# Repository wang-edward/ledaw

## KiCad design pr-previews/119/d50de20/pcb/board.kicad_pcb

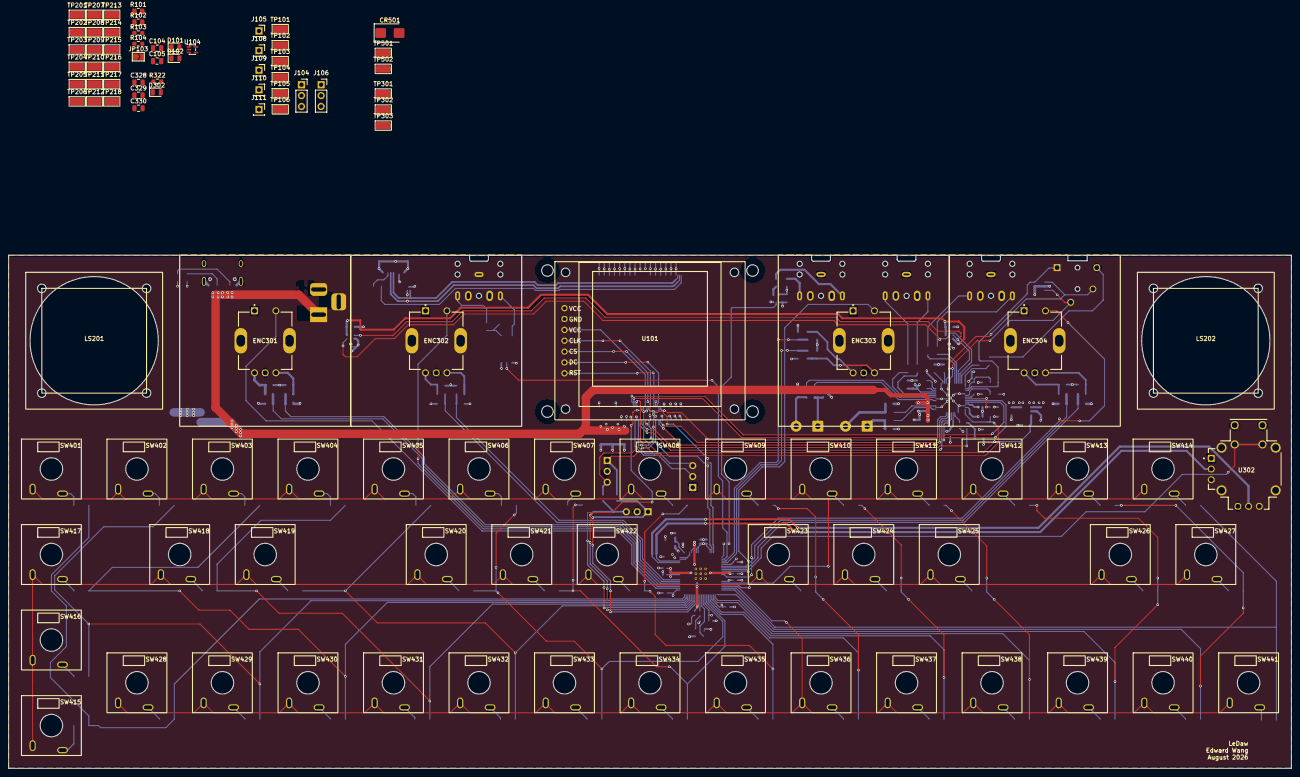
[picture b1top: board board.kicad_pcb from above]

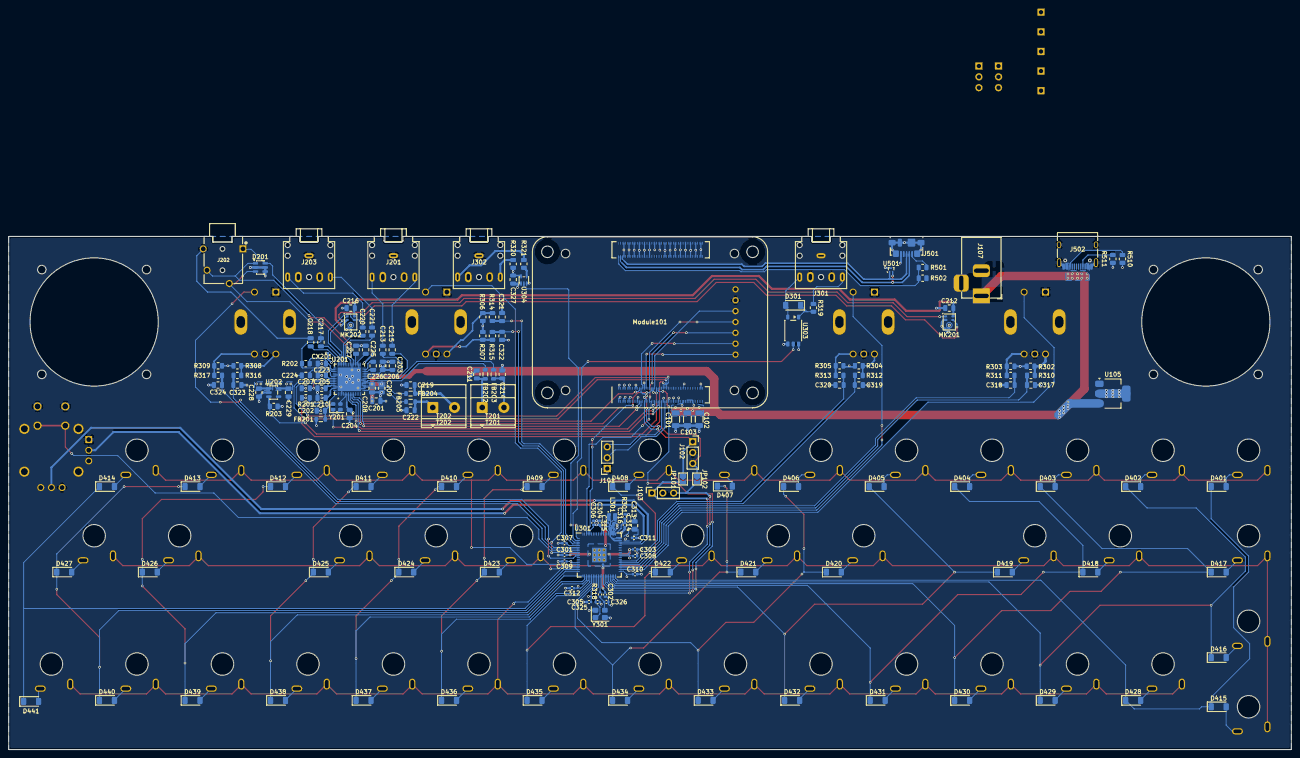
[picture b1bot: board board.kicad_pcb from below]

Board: 4 copper layers, 300.0 x 120.0 mm, 265 parts (164 on the bottom side), 172 nets.

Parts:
C101, C102, C103: 22uF X5R 16V; C_1206_3216Metric
C104: 10 uF, 10 V, X7R ceramic; C_0805_2012Metric
C105: 10-22 µF, 10 V tantalum, ESR 0.033-2.2 Ω over ope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; C_0805_2012Metric
C201, C203, C213, C215, C313: 10uF; C_0805_2012Metric
C202, C204, C210, C212, C216, C327, C328, C329, C330: 100nF; C_0805_2012Metric
C205, C206, C207, C208, C209, C217, C218, C220, C221, C223, C225, C226, C227, C228, C229: 1uF; C_0805_2012Metric
C211, C214, C219, C222: 470pF; C_0805_2012Metric
C224: 2.2uF; C_0805_2012Metric
C301, C303, C304, C305, C306, C307, C308, C309, C310, C311, C312: 100nF; C_0402_1005Metric
C302, C314: 4.7uF; C_0402_1005Metric
C315, C316: 4.7uF; C_0402_1005Metric_small_pads
C317, C318, C319, C320, C321, C322, C323, C324: 10nF; C_0805_2012Metric
C325, C326: 15pF; C_0402_1005Metric
CR501: SMBJ5.0A-TR; D_SMB
CX201: 1uF; C_0805_2012Metric
D101: LED Green; LED_0805_2012Metric
D102: LED Red; LED_0805_2012Metric
D201: ESDA6V1BC6; SOT-23-6
D301, D401, D402, D403, D404, D405, D406, D407, D408, D409, D410, D411, D412, D413, D414, D415, D416, D417, D418, D419, D420, D421, D422, D423, D424, D425, D426, D427, D428, D429, D430, D431, D432, D433, D434, D435, D436, D437, D438, D439, D440, D441: LL4148; D_MiniMELF
D302: LED Blue; LED_0805_2012Metric
ENC301, ENC302, ENC303, ENC304: RotaryEncoder_Switch; XDCR_PEC11R-4015F-S0024
FB201, FB202, FB203, FB204, FB205: 600Ohm@100MHz; L_0805_2012Metric
J101: CM4_UART; PinSocket_1x03_P2.54mm_Vertical
J102: CM4_DEBUG; PinSocket_1x03_P2.54mm_Vertical
J103: MCU_DEBUG; PinSocket_1x03_P2.54mm_Vertical
J104: MCU_UART; PinSocket_1x03_P2.54mm_Vertical
J105: MCU_RUN; PinSocket_1x01_P2.54mm_Vertical
J106: CM4_STATUS; PinSocket_1x03_P2.54mm_Vertical
J107: Barrel_5V; DC-005-5A-2.0
J108: TP_3V3; PinSocket_1x01_P2.54mm_Vertical
J109: TP_1V8; PinSocket_1x01_P2.54mm_Vertical
J110: TP_5V; PinSocket_1x01_P2.54mm_Vertical
J111: TP_GND; PinSocket_1x01_P2.54mm_Vertical
J201: LineOut; Jack_3.5mm_CUI_SJ1-3525N_Horizontal
J202: Headphone; CUI_SJ-43514
J203: LineIn; Jack_3.5mm_CUI_SJ1-3525N_Horizontal
J301: MidiIn; Jack_3.5mm_CUI_SJ1-3525N_Horizontal
J302: MidiOut; Jack_3.5mm_CUI_SJ1-3525N_Horizontal
J501: USB_B_Micro; USB_Micro-B_Molex_47346-0001
J502: USB_C_Receptacle_PowerOnly_24P; USB_C_Receptacle_HRO_TYPE-C-31-M-12
JP101, JP103: Jumper_SWCLK_Open; SolderJumper-2_P1.3mm_Open_TrianglePad1.0x1.5mm
JP102: Jumper_SWD_Open; SolderJumper-2_P1.3mm_Open_TrianglePad1.0x1.5mm
L301: 3.3uH; L_pol_2016
LS201: SpeakerL; bf-32-s-8ohm
LS202: SpeakerR; bf-32-s-8ohm
MK201: MicL; Knowles_LGA-5_3.5x2.65mm
MK202: MicR; Knowles_LGA-5_3.5x2.65mm
Module101: ComputeModule4-CM4; Raspberry-Pi-4-Compute-Module
R101, R102: 1k; R_0805_2012Metric
R103, R104: 4.7k; R_0603_1608Metric_Pad0.98x0.95mm_HandSolder
R201, R203, R302, R303, R304, R305, R306, R307, R308, R309, R310, R311, R312, R313, R314, R315, R316, R317: 10k; R_0805_2012Metric
R202: 2.2k; R_0805_2012Metric
R301: 33; R_0402_1005Metric
R318: 1k; R_0402_1005Metric
R319: 220; R_0805_2012Metric
R320: 33; R_0805_2012Metric
R321: 10; R_0805_2012Metric
R322: 1k; R_0603_1608Metric_Pad0.98x0.95mm_HandSolder
R501, R502: 2.2K 1%; R_0805_2012Metric
R510, R511: 5.1k; R_0805_2012Metric
SW401, SW402, SW403, SW404, SW405, SW406, SW407, SW408, SW409, SW410, SW411, SW412, SW413, SW414, SW415, SW416, SW417, SW418, SW419, SW420, SW421, SW422, SW423, SW424, SW425, SW426, SW427, SW428, SW429, SW430, SW431, SW432, SW433, SW434, SW435, SW436, SW437, SW438, SW439, SW440, SW441: SW_Push; ks-33-2.0
T201: TerminalL; TerminalBlock_Phoenix_MKDS-1,5-2-5.08_1x02_P5.08mm_Horizont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
T202: TerminalR; TerminalBlock_Phoenix_MKDS-1,5-2-5.08_1x02_P5.08mm_Horizont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
TP101: LDO_IN; TestPoint_Keystone_5015_Micro_Mini
TP102: LDO_OUT; TestPoint_Keystone_5015_Micro_Mini
TP103: CM4_5V; TestPoint_Keystone_5015_Micro_Mini
TP104: MCU_3V3_OUTPUT; TestPoint_Keystone_5015_Micro_Mini
TP105: MCU_1V8_OUTPUT; TestPoint_Keystone_5015_Micro_Mini
TP106: nLED_ACTIVITY; TestPoint_Keystone_5015_Micro_Mini
TP201: CODEC_MCLK; TestPoint_Keystone_5015_Micro_Mini
TP202: SPKLP; TestPoint_Keystone_5015_Micro_Mini
TP203: JACKSENSE; TestPoint_Keystone_5015_Micro_Mini
TP204: RECP; TestPoint_Keystone_5015_Micro_Mini
TP205: SPKLN; TestPoint_Keystone_5015_Micro_Mini
TP206: RECN; TestPoint_Keystone_5015_Micro_Mini
TP207: MICBIAS; TestPoint_Keystone_5015_Micro_Mini
TP208, TP213: INA1; TestPoint_Keystone_5015_Micro_Mini
TP209: HPR; TestPoint_Keystone_5015_Micro_Mini
TP210: SPKRP; TestPoint_Keystone_5015_Micro_Mini
TP211, TP215: INA2; TestPoint_Keystone_5015_Micro_Mini
TP212: HPL; TestPoint_Keystone_5015_Micro_Mini
TP214: HPSNS; TestPoint_Keystone_5015_Micro_Mini
TP216: SPKRN; TestPoint_Keystone_5015_Micro_Mini
TP217: AUDIO_LDO_IN; TestPoint_Keystone_5015_Micro_Mini
TP218: AUDIO_LDO_OUT; TestPoint_Keystone_5015_Micro_Mini
TP301: MCU_3V3; TestPoint_Keystone_5015_Micro_Mini
TP302: MCU_1V1; TestPoint_Keystone_5015_Micro_Mini
TP303: MCU_VREG_AVDD; TestPoint_Keystone_5015_Micro_Mini
TP501: VBUS; TestPoint_Keystone_5015_Micro_Mini
TP502: USB_OTG_ID; TestPoint_Keystone_5015_Micro_Mini
U101: Oled; waveshare-1.5inch-oled
U104: 74LVC1G07SE-7; SOT-353_SC-70-5
U105: NCP1117-3.3_SOT223; SOT-223-3_TabPin2
U201: MAX98089ETN_T
U202: TPS7A2018PDBVR; SOT-23-5
U301: RP2354B_80QFN; RP2350-QFN-80-1EP_10x10_P0.4mm_EP3.4x3.4mm_ThermalVias
U302: THB001P
U303: TLP2310; SO-5-6_4.55x3.7mm_P1.27mm
U304: 74AHC1G125DCKR; SOT-353_SC-70-5
U501: TPD2EUSB30; Texas_DRT-3
Y201: 12.288MHz; Oscillator_SMD_SeikoEpson_SG210-4Pin_2.5x2.0mm
Y301: ABM8-272-T3; Crystal_SMD_3225-4Pin_3.2x2.5mm

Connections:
+1V1: C301.1, C302.1, C303.1, C316.1, L301.1, TP302.1 (1_1), U301.10 (DVDD), U301.32 (DVDD), U301.51 (DVDD), U301.65 (VREG_FB)
+1V8: C203.2, C205.2, C206.2, C207.2, C212.2, C216.2, C229.1, J109.1 (Pin_1_1), MK201.5 (VDD), MK202.2 (SEL), MK202.5 (VDD), TP218.1 (1_1), U201.25 (PVDD), U201.50 (AVDD), U201.53 (DVDD), U202.5 (OUT)
+3V3: C105.1, C204.2, C210.2, C228.1, C304.1, C305.1, C306.1, C307.1, C308.1, C309.1, C310.1, C311.1, C312.1, C313.1, C315.1, C327.1, C328.1, D101.2 (A), D102.2 (A), D302.2 (A), FB201.2, J108.1 (Pin_1_1), JP103.1 (A), R103.1, R104.1, R201.2, R301.1, R302.1, R303.1, R304.1, R305.1, R306.1, R307.1, R308.1, R309.1, R320.2, TP102.1 (1_1), TP217.1 (1_1), TP301.1 (1_1), U101.1 (VCC), U104.5 (VCC), U105.2 (VO), U201.6 (DVDDS1), U201.55 (DVDDS2), U202.1 (IN), U301.5 (IOVDD), U301.15 (IOVDD), U301.24 (IOVDD), U301.29 (IOVDD), U301.41 (IOVDD), U301.50 (IOVDD), U301.59 (ADC_AVDD), U301.60 (IOVDD), U301.64 (VREG_VIN), U301.68 (USB_OTP_VDD), U301.69 (QSPI_IOVDD), U301.76 (IOVDD), U302.VR1_3, U302.VR2_3, U303.6 (VDD), U304.5 (VCC)
+5V: C101.1, C102.1, C103.1, C104.1, C201.2, C208.2, C209.2, CR501.1, J107.1, J110.1 (Pin_1_1), J502.A4 (VBUS), J502.A9 (VBUS), J502.B4 (VBUS), J502.B9 (VBUS), Module101.77 (+5v_(Input)), Module101.79 (+5v_(Input)), Module101.81 (+5v_(Input)), Module101.83 (+5v_(Input)), Module101.85 (+5v_(Input)), Module101.87 (+5v_(Input)), TP101.1 (1_1), TP103.1 (1_1), TP501.1 (1_1), U105.3 (VI), U201.18 (SPKRVDD), U201.19 (SPKLVDD)
/CODEC_1V8EN: Module101.46 (GPIO22), R203.1, U202.3 (EN)
/CODEC_CLKEN: Module101.47 (GPIO23), Y201.1 (OE)
/CODEC_~IRQ: Module101.54 (GPIO4), R201.1, U201.56 (~IRQ)
/DC: Module101.30 (GPIO6), U101.6 (DC)
/Global_EN: J106.1, Module101.99 (Global_EN)
/I2C1_SCL: Module101.56 (GPIO3), R104.2, U201.51 (SCL)
/I2C1_SDA: Module101.58 (GPIO2), R103.2, U201.52 (SDA)
/MCU_SWCLK: J103.1, JP101.2 (B), U301.33 (SWCLK)
/MCU_SWD: J103.3, JP102.2 (B), U301.34 (SWD)
/PCM_CLK: Module101.49 (GPIO18), U201.8 (BCLKS1)
/PCM_DIN: Module101.27 (GPIO20), U201.7 (SDOUTS1)
/PCM_DOUT: Module101.25 (GPIO21), U201.9 (SDINS1)
/PCM_FS: Module101.26 (GPIO19), U201.10 (LRCLKS1)
/RST: Module101.34 (GPIO5), U101.7 (RST)
/RUN: J105.1 (Pin_1_1), JP103.2 (B), Module101.48 (GPIO27), U301.35 (RUN)
/RUN_PG: J106.2, Module101.92 (RUN_PG)
/SPI0_CE1: Module101.37 (GPIO7), U101.5 (CS)
/SPI0_MOSI: Module101.44 (GPIO10), U101.3 (DIN)
/SPI0_SCLK: Module101.38 (GPIO11), U101.4 (CLK)
/SWCLK: J102.1, JP101.1 (A), Module101.31 (GPIO12)
/SWD: J102.3, JP102.1 (A), Module101.28 (GPIO13)
/UART0_RX: J101.3, Module101.51 (GPIO15)
/UART0_TX: J101.2, Module101.55 (GPIO14)
/UART4_RX: J104.2, Module101.40 (GPIO9), U301.77 (GPIO0)
/UART4_TX: J104.3, Module101.39 (GPIO8), U301.78 (GPIO1)
/USB2_N: J501.2 (D-), Module101.103 (USB2_N), U501.2 (D-)
/USB2_OTG_ID: Module101.101 (USB_OTG_ID), R501.2, R502.1, TP502.1 (1_1)
/USB2_P: J501.3 (D+), Module101.105 (USB2_P), U501.1 (D+)
/audio/C1N: C226.1, U201.27 (C1N)
/audio/C1P: C226.2, U201.26 (C1P)
/audio/DIGMICCLK: MK201.4 (CLOCK), MK202.4 (CLOCK), U201.41 (MIC1N/DIGMICCLK)
/audio/DIGMICDATA: MK201.1 (DATA), MK202.1 (DATA), U201.40 (MIC1P/DIGMICDATA)
/audio/JACKSENSE: C217.1, D201.6 (TVS4), J202.S, R202.2, TP203.1 (1_1), U201.45 (JACKSNS)
/mcu/ENC1_A: C317.1, R310.2, U301.44 (GPIO35)
/mcu/ENC1_B: C318.1, R311.2, U301.45 (GPIO36)
/mcu/ENC1_SW: ENC301.S2, U301.42 (GPIO33)
/mcu/ENC2_A: C319.1, R312.2, U301.46 (GPIO37)
/mcu/ENC2_B: C320.1, R313.2, U301.47 (GPIO38)
/mcu/ENC2_SW: ENC302.S2, U301.43 (GPIO34)
/mcu/ENC3_A: C321.1, R314.2, U301.3 (GPIO6)
/mcu/ENC3_B: C322.1, R315.2, U301.4 (GPIO7)
/mcu/ENC3_SW: ENC303.S2, U301.9 (GPIO11)
/mcu/ENC4_A: C323.1, R316.2, U301.6 (GPIO8)
/mcu/ENC4_B: C324.1, R317.2, U301.7 (GPIO9)
/mcu/ENC4_SW: ENC304.S2, U301.11 (GPIO12)
/mcu/HEARTBEAT: R322.2, U301.48 (GPIO39)
/mcu/JOYSTICK_SW: U301.8 (GPIO10), U302.A, U302.B
/mcu/JOYSTICK_X: C329.1, U301.58 (GPIO47_ADC7), U302.VR1_2
/mcu/JOYSTICK_Y: C330.1, U301.57 (GPIO46_ADC6), U302.VR2_2
/mcu/MIDI_RX: U301.2 (GPIO5), U303.5 (VO)
/mcu/MIDI_TX: U301.1 (GPIO4), U304.2
/mcu/VREG_AVDD: C314.1, R301.2, TP303.1 (1_1), U301.61 (VREG_AVDD)
/mcu/VREG_LX: L301.2, U301.63 (VREG_LX)
/mcu/XIN: C325.1, U301.30 (XIN), Y301.1
/mcu/XOUT: R318.1, U301.31 (XOUT)
/mcu/matrix_C0: D401.1 (K), D415.1 (K), D428.1 (K), U301.40 (GPIO32)
/mcu/matrix_C1: D402.1 (K), D416.1 (K), D429.1 (K), U301.39 (GPIO31)
/mcu/matrix_C2: D403.1 (K), D417.1 (K), D430.1 (K), U301.38 (GPIO30)
/mcu/matrix_C3: D404.1 (K), D418.1 (K), D431.1 (K), U301.37 (GPIO29)
/mcu/matrix_C4: D405.1 (K), D419.1 (K), D432.1 (K), U301.36 (GPIO28)
/mcu/matrix_C5: D406.1 (K), D420.1 (K), D433.1 (K), U301.28 (GPIO27)
/mcu/matrix_C6: D407.1 (K), D421.1 (K), D434.1 (K), U301.27 (GPIO26)
/mcu/matrix_C7: D408.1 (K), D422.1 (K), D435.1 (K), U301.26 (GPIO25)
/mcu/matrix_C8: D409.1 (K), D423.1 (K), D436.1 (K), U301.25 (GPIO24)
/mcu/matrix_C9: D410.1 (K), D424.1 (K), D437.1 (K), U301.23 (GPIO23)
/mcu/matrix_C10: D411.1 (K), D425.1 (K), D438.1 (K), U301.22 (GPIO22)
/mcu/matrix_C11: D412.1 (K), D426.1 (K), D439.1 (K), U301.21 (GPIO21)
/mcu/matrix_C12: D413.1 (K), D427.1 (K), D440.1 (K), U301.20 (GPIO20)
/mcu/matrix_C13: D414.1 (K), D441.1 (K), U301.19 (GPIO19)
/mcu/matrix_R0: SW401.1, SW402.1, SW403.1, SW404.1, SW405.1, SW406.1, SW407.1, SW408.1, SW409.1, SW410.1, SW411.1, SW412.1, SW413.1, SW414.1, U301.16 (GPIO16)
/mcu/matrix_R1: SW415.1, SW416.1, SW417.1, SW418.1, SW419.1, SW420.1, SW421.1, SW422.1, SW423.1, SW424.1, SW425.1, SW426.1, SW427.1, U301.17 (GPIO17)
/mcu/matrix_R2: SW428.1, SW429.1, SW430.1, SW431.1, SW432.1, SW433.1, SW434.1, SW435.1, SW436.1, SW437.1, SW438.1, SW439.1, SW440.1, SW441.1, U301.18 (GPIO18)
/nLED_Activity: Module101.21 (PI_nLED_Activity), R101.2, TP106.1 (1_1)
/nPWR_LED: Module101.95 (nPI_LED_PWR), U104.2
/nRPIBOOT: J106.3, Module101.93 (nRPIBOOT)
GND: C101.2, C102.2, C103.2, C104.2, C105.2, C201.1, C202.1, C203.1, C204.1, C205.1, C206.1, C207.1, C208.1, C209.1, C210.1, C211.2, C212.1, C214.2, C216.1, C218.1, C219.2, C222.2, C223.2, C224.2, C225.2, C227.2, C228.2, C229.2, C301.2, C302.2, C303.2, C304.2, C305.2, C306.2, C307.2, C308.2, C309.2, C310.2, C311.2, C312.2, C313.2, C314.2, C315.2, C316.2, C317.2, C318.2, C319.2, C320.2, C321.2, C322.2, C323.2, C324.2, C325.2, C326.2, C327.2, C328.2, C329.2, C330.2, CR501.2, CX201.1, D201.2 (COM), D201.4 (TVS3), D201.5 (COM), ENC301.C, ENC301.S1, ENC302.C, ENC302.S1, ENC303.C, ENC303.S1, ENC304.C, ENC304.S1, J101.1, J102.2, J103.2, J104.1, J107.2, J111.1 (Pin_1_1), J201.S, J202.R2, J203.S, J302.S, J501.5 (GND), J501.SH (Shield), J502.A1 (GND), J502.A12 (GND), J502.B1 (GND), J502.B12 (GND), J502.SH (SHIELD), MK201.2 (SEL), MK201.3 (GND), MK202.3 (GND), Module101.1 (GND), Module101.2 (GND), Module101.7 (GND), Module101.8 (GND), Module101.13 (GND), Module101.14 (GND), Module101.22 (GND), Module101.23 (GND), Module101.32 (GND), Module101.33 (GND), Module101.42 (GND), Module101.43 (GND), Module101.52 (GND), Module101.53 (GND), Module101.59 (GND), Module101.60 (GND), Module101.65 (GND), Module101.66 (GND), Module101.71 (GND), Module101.74 (GND), Module101.98 (GND), Module101.107 (GND), Module101.108 (GND), Module101.113 (GND), Module101.114 (GND), Module101.119 (GND), Module101.120 (GND), Module101.125 (GND), Module101.126 (GND), Module101.131 (GND), Module101.132 (GND), Module101.137 (GND), Module101.138 (GND), Module101.144 (GND), Module101.150 (GND), Module101.155 (GND), Module101.156 (GND), Module101.161 (GND), Module101.162 (GND), Module101.167 (GND), Module101.168 (GND), Module101.173 (GND), Module101.174 (GND), Module101.179 (GND), Module101.180 (GND), Module101.185 (GND), Module101.186 (GND), Module101.191 (GND), Module101.192 (GND), Module101.197 (GND), Module101.198 (GND), R203.2, R502.2, R510.2, R511.2, TP214.1 (1_1), U101.2 (GND), U104.3 (GND), U105.1 (GND), U201.3 (DGND), U201.16 (SPKRGND), U201.21 (SPKLGND), U201.30 (HPGND), U201.34 (HPSNS), U201.47 (AGND), U201.54 (SDINS2), U201.57 (EP), U202.2 (GND), U301.62 (VREG_PGND), U301.81 (GND), U302.C, U302.D, U302.VR1_1, U302.VR2_1, U303.4 (GND), U304.1, U304.3 (GND), U501.3 (GND), Y201.2 (GND), Y301.2, Y301.4
unnamed: C213.2, J201.T, TP204.1 (1_1)
unnamed: C215.2, J201.R, TP206.1 (1_1)
unnamed: C220.1, J203.T
unnamed: C221.1, J203.R
unnamed: C326.1, R318.2, Y301.3
unnamed: D101.1 (K), R101.1
unnamed: D102.1 (K), R102.1
unnamed: D201.1 (TVS1), J202.T, TP212.1 (1_1), U201.33 (HPL)
unnamed: D201.3 (TVS2), J202.R1, TP209.1 (1_1), U201.35 (HPR)
unnamed: D301.2 (A), J301.T, U303.3 (K)
unnamed: D301.1 (K), R319.2, U303.1 (A)
unnamed: D302.1 (K), R322.1
unnamed: D401.2 (A), SW401.2
unnamed: D402.2 (A), SW402.2
unnamed: D403.2 (A), SW403.2
unnamed: D404.2 (A), SW404.2
unnamed: D405.2 (A), SW405.2
unnamed: D406.2 (A), SW406.2
unnamed: D407.2 (A), SW407.2
unnamed: D408.2 (A), SW408.2
unnamed: D409.2 (A), SW409.2
unnamed: D410.2 (A), SW410.2
unnamed: D411.2 (A), SW411.2
unnamed: D412.2 (A), SW412.2
unnamed: D413.2 (A), SW413.2
unnamed: D414.2 (A), SW414.2
unnamed: D415.2 (A), SW415.2
unnamed: D416.2 (A), SW416.2
unnamed: D417.2 (A), SW417.2
unnamed: D418.2 (A), SW418.2
unnamed: D419.2 (A), SW419.2
unnamed: D420.2 (A), SW420.2
unnamed: D421.2 (A), SW421.2
unnamed: D422.2 (A), SW422.2
unnamed: D423.2 (A), SW423.2
unnamed: D424.2 (A), SW424.2
unnamed: D425.2 (A), SW425.2
unnamed: D426.2 (A), SW426.2
unnamed: D427.2 (A), SW427.2
unnamed: D428.2 (A), SW428.2
unnamed: D429.2 (A), SW429.2
unnamed: D430.2 (A), SW430.2
unnamed: D431.2 (A), SW431.2
unnamed: D432.2 (A), SW432.2
unnamed: D433.2 (A), SW433.2
unnamed: D434.2 (A), SW434.2
unnamed: D435.2 (A), SW435.2
unnamed: D436.2 (A), SW436.2
unnamed: D437.2 (A), SW437.2
unnamed: D438.2 (A), SW438.2
unnamed: D439.2 (A), SW439.2
unnamed: D440.2 (A), SW440.2
unnamed: D441.2 (A), SW441.2
unnamed: ENC301.A, R302.2, R310.1
unnamed: ENC301.B, R303.2, R311.1
unnamed: ENC302.A, R304.2, R312.1
unnamed: ENC302.B, R305.2, R313.1
unnamed: ENC303.A, R306.2, R314.1
unnamed: ENC303.B, R307.2, R315.1
unnamed: ENC304.A, R308.2, R316.1
unnamed: ENC304.B, R309.2, R317.1
unnamed: J301.R, R319.1
unnamed: J302.R, R320.1
unnamed: J302.T, R321.2
unnamed: J501.1 (VBUS), R501.1
unnamed: J502.A5 (CC1), R511.1
unnamed: J502.B5 (CC2), R510.1
unnamed: Module101.88 (+1.8v_(Output)), Module101.90 (+1.8v_(Output)), TP105.1 (1_1)
unnamed: Module101.78 (GPIO_VREF(1.8v/3.3v_Input)), Module101.84 (+3.3v_(Output)), Module101.86 (+3.3v_(Output)), TP104.1 (1_1)
unnamed: R102.2, U104.4
unnamed: R321.1, U304.4
unnamed: C211.1, FB202.2, T201.1, TP202.1 (1_1)
unnamed: C214.1, FB203.2, T201.2, TP205.1 (1_1)
unnamed: C222.1, FB205.2, T202.1, TP216.1 (1_1)
unnamed: C219.1, FB204.2, T202.2, TP210.1 (1_1)
unnamed: C227.1, U201.32 (HPVDD)
unnamed: C225.1, U201.31 (HPVSS)
unnamed: C220.2, TP213.1 (1_1), U201.39 (INA1/EXTMICP)
unnamed: C221.2, TP215.1 (1_1), U201.38 (INA2/EXTMICN)
unnamed: TP201.1 (1_1), U201.5 (MCLK), Y201.3 (OUT)
unnamed: C218.2, TP211.1 (1_1), U201.43 (MIC2N)
unnamed: C217.2, TP208.1 (1_1), U201.42 (MIC2P)
unnamed: CX201.2, R202.1, TP207.1 (1_1), U201.44 (MICBIAS)
unnamed: C215.1, U201.23 (RECN/LOUTR/RXINN)
unnamed: C213.1, U201.24 (RECP/LOUTL/RXINP)
unnamed: C224.1, U201.48 (REF)
unnamed: C223.1, U201.49 (REG)
unnamed: FB203.1, U201.22 (SPKLN)
unnamed: FB202.1, U201.20 (SPKLP)
unnamed: FB205.1, U201.15 (SPKRN)
unnamed: FB204.1, U201.17 (SPKRP)
unnamed: C202.2, FB201.1, Y201.4 (Vcc)
